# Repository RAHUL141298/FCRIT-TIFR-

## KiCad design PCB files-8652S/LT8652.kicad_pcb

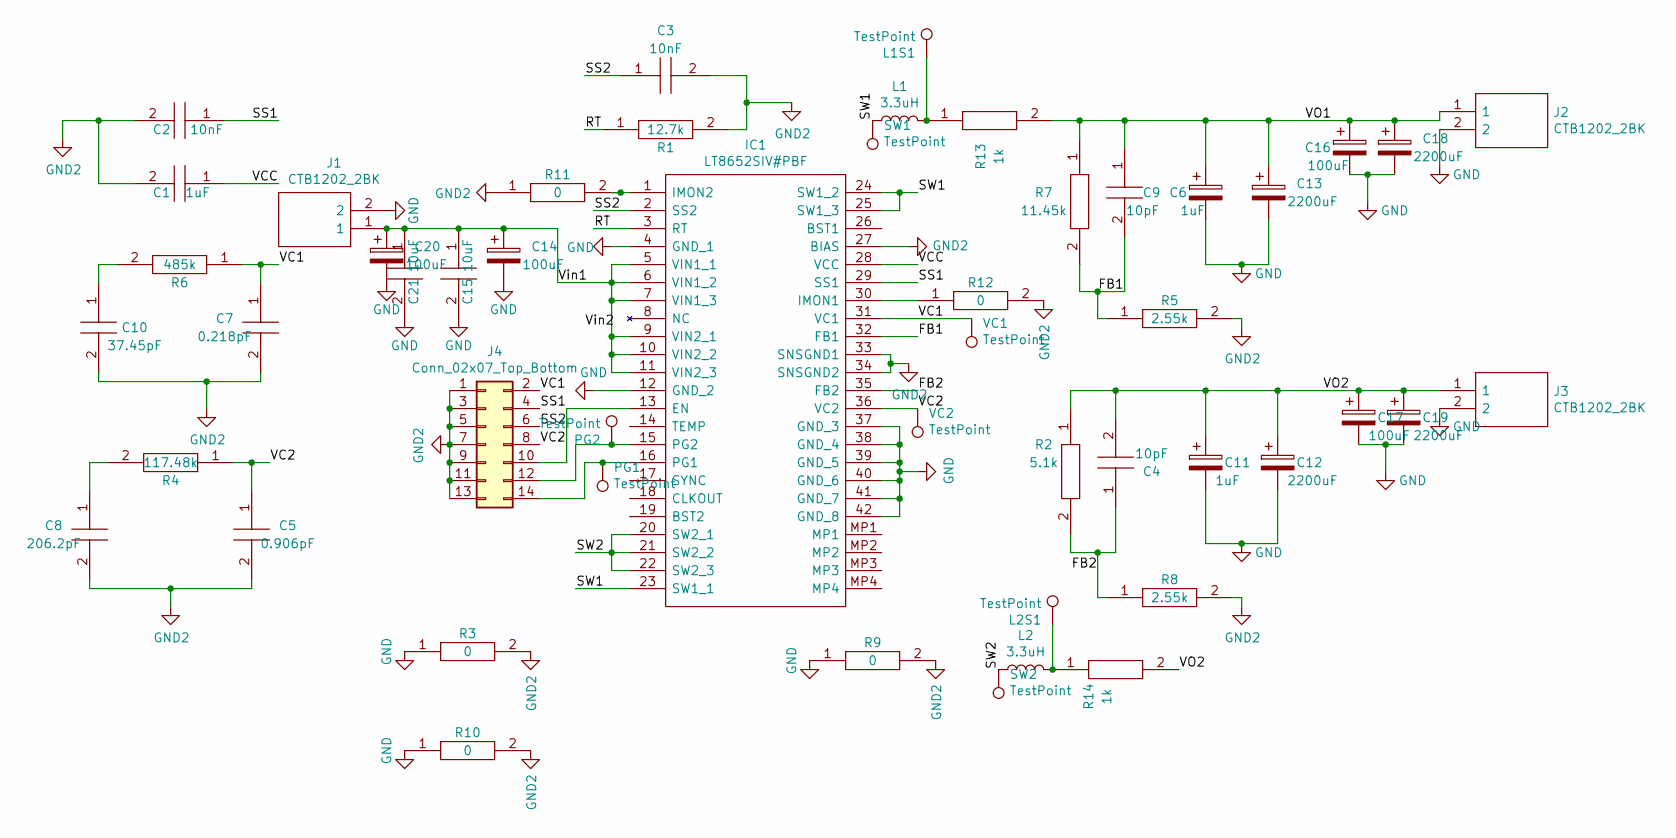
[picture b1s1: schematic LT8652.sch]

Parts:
C1: 1uF; C_0603_1608Metric_Pad1.05x0.95mm_HandSolder; Mouser Part Number 603-C0603JRNPO9BN100
C2: 10nF; C_0603_1608Metric_Pad1.05x0.95mm_HandSolder; Mouser Part Number 603-C0603JRNPO9BN100
C3: 10nF; C_0603_1608Metric_Pad1.05x0.95mm_HandSolder; Mouser Part Number 80-C0603C103K5R
C4, C9: 10pF; C_0603_1608Metric_Pad1.05x0.95mm_HandSolder; Mouser Part Number 603-C0603JRNPO9BN100
C5: 0.906pF; C_0603_1608Metric_Pad1.05x0.95mm_HandSolder; Mouser Part Number 603-C0603JRNPO9BN100
C6, C11: 1uF; C_0603_1608Metric_Pad1.05x0.95mm_HandSolder
C7: 0.218pF; C_0603_1608Metric_Pad1.05x0.95mm_HandSolder; Mouser Part Number 603-C0603JRNPO9BN100
C8: 206.2pF; C_0603_1608Metric_Pad1.05x0.95mm_HandSolder; Mouser Part Number 603-C0603JRNPO9BN100
C10: 37.45pF; C_0603_1608Metric_Pad1.05x0.95mm_HandSolder; Mouser Part Number 603-C0603JRNPO9BN100
C12, C13, C18, C19: 2200uF; CAPAE1350X1400N
C14, C20: 100uF; CP_Elec_8x10.5
C15, C21: 10uF; C_0603_1608Metric_Pad1.05x0.95mm_HandSolder; Mouser Part Number 603-C0603JRNPO9BN100
C16, C17: 100uF; C_0603_1608Metric_Pad1.05x0.95mm_HandSolder
IC1: LT8652SIV#PBF; LT8652SIVPBF; Manufacturer_Part_Number LT8652SIV#PBF
J1, J2, J3: CTB1202_2BK; TerminalBlock_TE_282834-2_1x02_P2.54mm_Horizontal; Manufacturer_Part_Number CTB1202/2BK
J4: Conn_02x07_Top_Bottom; PinHeader_2x07_P2.54mm_Vertical
L1, L2: 3.3uH; SRP1038C4R7M
L1S1, L2S1: TestPoint; TestPoint_Pad_D2.0mm
PG1, PG2: TestPoint; TestPoint_Pad_D2.0mm
R1: 12.7k; R_0603_1608Metric_Pad1.05x0.95mm_HandSolder; Manufacturer_Part_Number CRCW060312K7FKEA; Mouser Part Number 71-CRCW0603-12.7K-E3
R2: 5.1k; R_0603_1608Metric_Pad1.05x0.95mm_HandSolder; Mouser Part Number 667-ERA-2AEB512X
R3, R9, R10, R11, R12: 0; R_0603_1608Metric_Pad1.05x0.95mm_HandSolder; Mouser Part Number 756-PCF0805R2K55BI
R4: 117.48k; R_0603_1608Metric_Pad1.05x0.95mm_HandSolder; Mouser Part Number 756-PCF0805R2K55BI
R5, R8: 2.55k; R_0603_1608Metric_Pad1.05x0.95mm_HandSolder; Mouser Part Number 756-PCF0805R2K55BI
R6: 485k; R_0603_1608Metric_Pad1.05x0.95mm_HandSolder; Mouser Part Number 756-PCF0805R2K55BI
R7: 11.45k; R_0603_1608Metric_Pad1.05x0.95mm_HandSolder; Mouser Part Number 667-ERA-2AEB512X
R13, R14: 1k; R_2512_6332Metric_Pad1.52x3.35mm_HandSolder; Mouser Part Number 667-ERA-2AEB512X
SW1, SW2: TestPoint; TestPoint_Pad_D2.0mm
VC1, VC2: TestPoint; TestPoint_Pad_D2.0mm

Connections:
/FB1: C9.2, IC1.32 (FB1), R5.1, R7.2
/FB2: C4.1, IC1.35 (FB2), R2.2, R8.1
/RT: IC1.3 (RT), R1.1
/SS1: C2.1, IC1.29 (SS1), J4.4
/SS2: C3.1, IC1.2 (SS2), J4.6
/SW1: IC1.23 (SW1_1), IC1.24 (SW1_2), IC1.25 (SW1_3), L1.1, SW1.1
/SW2: IC1.20 (SW2_1), IC1.21 (SW2_2), IC1.22 (SW2_3), L2.1, SW2.1
/VC1: C7.1, IC1.31 (VC1), J4.2, R6.1, VC1.1
/VC2: C5.1, IC1.36 (VC2), J4.8, R4.1, VC2.1
/VCC: C1.1, IC1.28 (VCC)
/VO1: C6.1, C9.1, C13.1, C16.1, C18.1, J2.1, R7.1, R13.2
/VO2: C4.2, C11.1, C12.1, C17.1, C19.1, J3.1, R2.1, R14.2
/Vin1: C14.1, C15.1, C20.1, C21.1, IC1.5 (VIN1_1), IC1.6 (VIN1_2), IC1.7 (VIN1_3), IC1.9 (VIN2_1), IC1.10 (VIN2_2), IC1.11 (VIN2_3), J1.1
GND: C6.2, C11.2, C12.2, C13.2, C14.2, C15.2, C16.2, C17.2, C18.2, C19.2, C20.2, C21.2, IC1.4 (GND_1), IC1.12 (GND_2), IC1.37 (GND_3), IC1.38 (GND_4), IC1.39 (GND_5), IC1.40 (GND_6), IC1.41 (GND_7), IC1.42 (GND_8), J1.2, J2.2, J3.2, R3.1, R9.1, R10.1
GND2: C1.2, C2.2, C3.2, C5.2, C7.2, C8.2, C10.2, IC1.27 (BIAS), IC1.33 (SNSGND1), IC1.34 (SNSGND2), J4.1, J4.3, J4.5, J4.7, J4.9, J4.11, J4.13, R1.2, R3.2, R5.2, R8.2, R9.2, R10.2, R11.1, R12.2
unnamed: C8.1, R4.2
unnamed: C10.1, R6.2
unnamed: IC1.1 (IMON2), R11.2
unnamed: IC1.13 (EN), J4.10
unnamed: IC1.15 (PG2), J4.12, PG2.1
unnamed: IC1.16 (PG1), J4.14, PG1.1
unnamed: IC1.30 (IMON1), R12.1
unnamed: L1.2, L1S1.1, R13.1
unnamed: L2.2, L2S1.1, R14.1

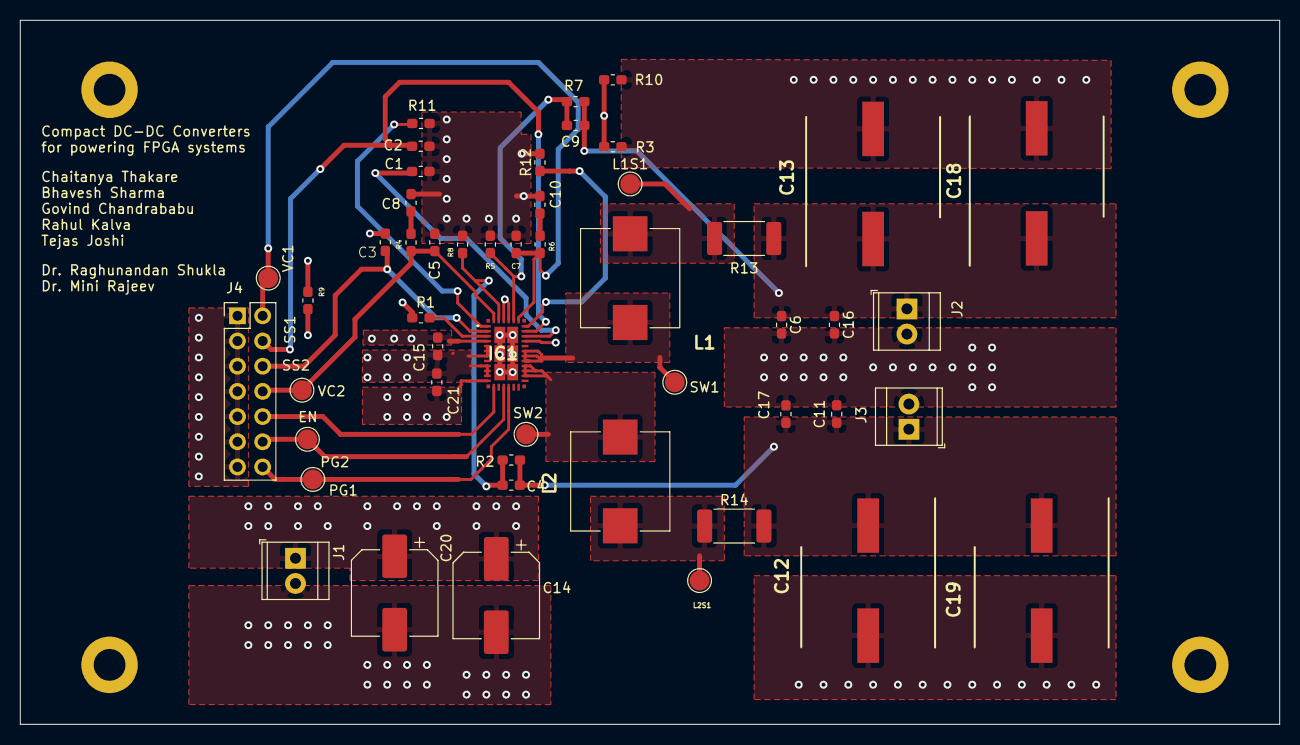
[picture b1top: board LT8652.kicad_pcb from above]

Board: 4 copper layers, 127.0 x 71.0 mm, 50 parts (0 on the bottom side), 24 nets.

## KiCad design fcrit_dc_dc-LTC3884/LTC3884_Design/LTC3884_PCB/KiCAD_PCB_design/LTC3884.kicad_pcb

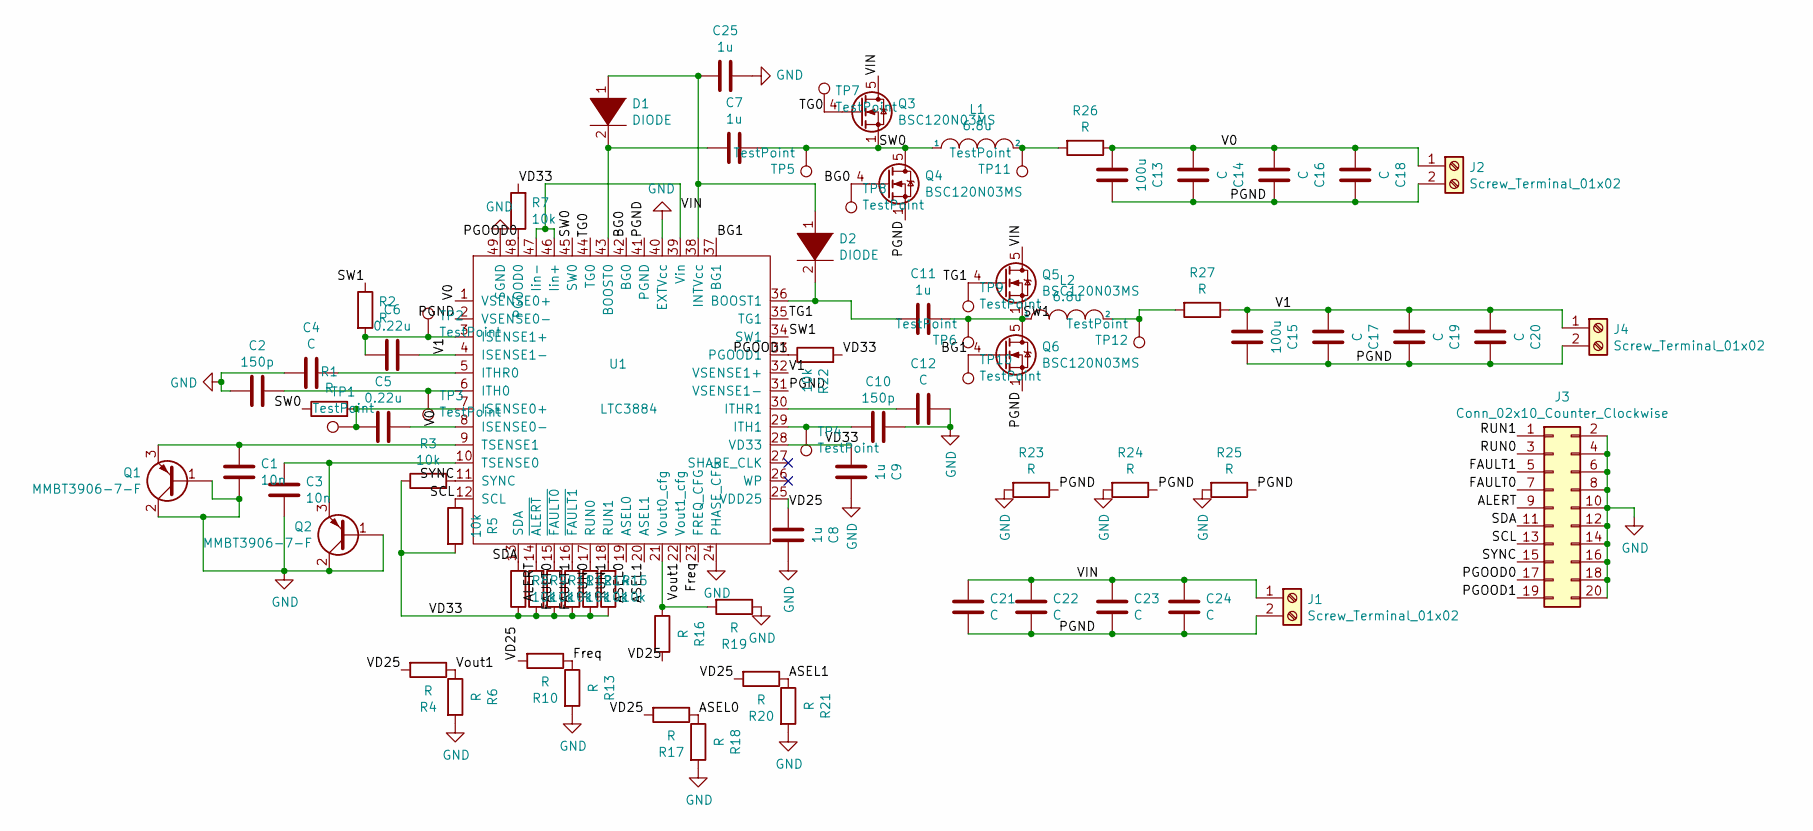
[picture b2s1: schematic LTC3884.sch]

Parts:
C1, C3: 10n; C_0603_1608Metric_Pad1.05x0.95mm_HandSolder
C2, C10: 150p; C_0603_1608Metric_Pad1.05x0.95mm_HandSolder
C4, C12, C16, C18, C19, C20, C23, C24: C; C_0603_1608Metric_Pad1.05x0.95mm_HandSolder
C5, C6: 0.22u; C_0603_1608Metric_Pad1.05x0.95mm_HandSolder
C7, C8, C9, C11, C25: 1u; C_0603_1608Metric_Pad1.05x0.95mm_HandSolder
C13, C15: 100u; CP_Elec_6.3x5.8
C14, C17, C21, C22: C; CP_Elec_6.3x5.8
D1, D2: DIODE; SOD2513X120N
J1, J2, J4: Screw_Terminal_01x02; TerminalBlock_TE_282834-2_1x02_P2.54mm_Horizontal
J3: Conn_02x10_Counter_Clockwise; PinHeader_2x10_P2.54mm_Vertical
L1, L2: 6.8u; SRP1038C6R8M
Q1, Q2: MMBT3906-7-F; SOT96P240X110-3N
Q3, Q4, Q5, Q6: BSC120N03MS; TDSON-8-1
R1, R2, R4, R6, R10, R13, R16, R17, R18, R19, R20, R21, R23, R24, R25: R; R_0603_1608Metric_Pad1.05x0.95mm_HandSolder
R3, R5, R7, R8, R9, R11, R12, R14, R15, R22: 10k; R_0603_1608Metric_Pad1.05x0.95mm_HandSolder
R26, R27: R; R_2512_6332Metric_Pad1.52x3.35mm_HandSolder
TP1, TP2, TP3, TP4, TP5, TP6, TP7, TP8, TP9, TP10, TP11, TP12: TestPoint; TestPoint_Pad_D2.0mm
U1: LTC3884; QFN-48-1EP_7x7mm_P0.5mm_EP5.15x5.15mm

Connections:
/ALERT: J3.9, R9.2, U1.14 (~ALERT)
/ASEL0: R17.1, R18.1, U1.19 (ASEL0)
/ASEL1: R20.1, R21.1, U1.20 (ASEL1)
/BG0: Q4.4 (G), TP8.1, U1.42 (BG0)
/BG1: Q6.4 (G), TP10.1, U1.37 (BG1)
/FAULT0: J3.7, R11.2, U1.15 (~FAULT0)
/FAULT1: J3.5, R12.2, U1.16 (~FAULT1)
/Freq: R10.1, R13.1, U1.23 (FREQ_CFG)
/PGND: C13.2, C14.2, C15.2, C16.2, C17.2, C18.2, C19.2, C20.2, C21.2, C22.2, C23.2, C24.2, J1.2, J2.2, J4.2, Q4.1 (S), Q4.2 (S), Q4.3 (S), Q6.1 (S), Q6.2 (S), Q6.3 (S), R23.1, R24.1, R25.1, U1.2 (VSENSE0-), U1.31 (VSENSE1-), U1.41 (PGND)
/PGOOD0: J3.17, R7.1, U1.48 (PGOOD0)
/PGOOD1: J3.19, R22.1, U1.33 (PGOOD1)
/RUN0: J3.3, R14.2, U1.17 (RUN0)
/RUN1: J3.1, R15.2, U1.18 (RUN1)
/SCL: J3.13, R5.1, U1.12 (SCL)
/SDA: J3.11, R8.2, U1.13 (SDA)
/SW0: C7.2, L1.1, Q3.1 (S), Q3.2 (S), Q3.3 (S), Q4.5 (D), R1.1, TP5.1, U1.45 (SW0)
/SW1: C11.2, L2.1, Q5.1 (S), Q5.2 (S), Q5.3 (S), Q6.5 (D), R2.1, TP6.1, U1.34 (SW1)
/SYNC: J3.15, R3.2, U1.11 (SYNC)
/TG0: Q3.4 (G), TP7.1, U1.44 (TG0)
/TG1: Q5.4 (G), TP9.1, U1.35 (TG1)
/V0: C5.2, C13.1, C14.1, C16.1, C18.1, J2.1, R26.1, U1.1 (VSENSE0+), U1.8 (ISENSE0-)
/V1: C6.2, C15.1, C17.1, C19.1, C20.1, J4.1, R27.1, U1.4 (ISENSE1-), U1.32 (VSENSE1+)
/VD25: C8.2, R4.2, R10.2, R16.2, R17.2, R20.2, U1.25 (VDD25)
/VD33: C9.2, R3.1, R5.2, R7.2, R8.1, R9.1, R11.1, R12.1, R14.1, R15.1, R22.2, U1.28 (VD33)
/VIN: C21.1, C22.1, C23.1, C24.1, J1.1, Q3.5 (D), Q5.5 (D), U1.39 (Vin), U1.46 (Iin+), U1.47 (Iin-)
/Vout1: R4.1, R6.1, U1.22 (Vout1_cfg)
GND: C1.2, C2.1, C3.2, C4.1, C8.1, C9.1, C10.2, C12.2, C25.2, J3.2, J3.4, J3.6, J3.8, J3.10, J3.12, J3.14, J3.16, J3.18, J3.20, Q1.1 (B), Q1.2 (C), Q2.1 (B), Q2.2 (C), R6.2, R13.2, R18.2, R19.1, R21.2, R23.2, R24.2, R25.2, U1.24 (PHASE_CFG), U1.40 (EXTVcc), U1.49 (SGND)
unnamed: C1.1, Q1.3 (E), U1.9 (TSENSE1)
unnamed: C2.2, TP3.1, U1.6 (ITH0)
unnamed: C3.1, Q2.3 (E), U1.10 (TSENSE0)
unnamed: C4.2, U1.5 (ITHR0)
unnamed: C5.1, R1.2, TP1.1, U1.7 (ISENSE0+)
unnamed: C6.1, R2.2, TP2.1, U1.3 (ISENSE1+)
unnamed: C7.1, D1.2 (A), U1.43 (BOOST0)
unnamed: C10.1, TP4.1, U1.29 (ITH1)
unnamed: C11.1, D2.2 (A), U1.36 (BOOST1)
unnamed: C12.1, U1.30 (ITHR1)
unnamed: C25.1, D1.1 (K), D2.1 (K), U1.38 (INTVcc)
unnamed: L1.2, R26.2, TP11.1
unnamed: L2.2, R27.2, TP12.1
unnamed: R16.1, R19.2, U1.21 (Vout0_cfg)

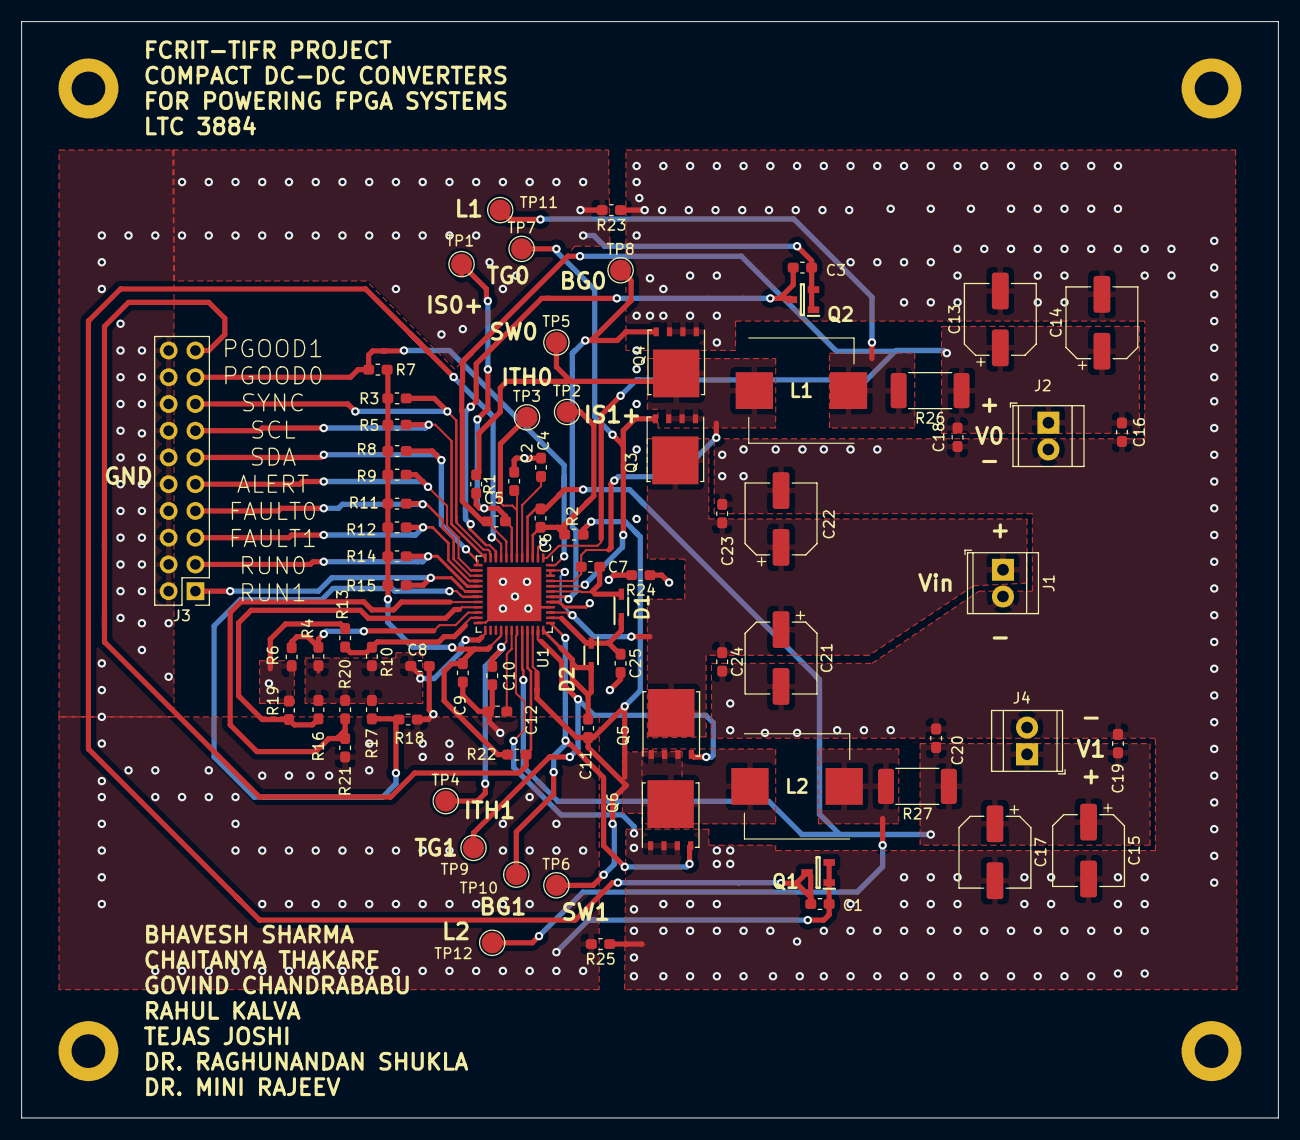
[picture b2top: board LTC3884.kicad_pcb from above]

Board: 4 copper layers, 119.4 x 104.1 mm, 79 parts (0 on the bottom side), 41 nets.

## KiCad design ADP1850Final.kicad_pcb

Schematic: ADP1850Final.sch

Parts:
C1, C16, C17: 6.8pF; C_0603_1608Metric_Pad1.05x0.95mm_HandSolder; Mouser Part Number 81-GRM33R6YA104KE14D
C2, C3, C8, C9: 1uF; C_0603_1608Metric_Pad1.05x0.95mm_HandSolder; Mouser Part Number 80-C0603C105K8R
C4, C5, C18, C19: 100uF; CP_Elec_6.3x5.8; Manufacturer_Part_Number EEHZA1V101P
C6: 68pF; C_0603_1608Metric_Pad1.05x0.95mm_HandSolder; Mouser Part Number 81-GRM33R6YA104KE14D
C7: 0.1nF; C_0603_1608Metric_Pad1.05x0.95mm_HandSolder; Mouser Part Number 81-GRM33R6YA104KE14D
C10: 1.5nF; C_0603_1608Metric_Pad1.05x0.95mm_HandSolder; Mouser Part Number 81-GRM33R6YA104KE14D
C11: 1nF; C_0603_1608Metric_Pad1.05x0.95mm_HandSolder; Mouser Part Number 81-GRM33R6YA104KE14D
C12: 56nF; C_0603_1608Metric_Pad1.05x0.95mm_HandSolder; Mouser Part Number 710-885012006022
C13: 56nF; C_0603_1608Metric_Pad1.05x0.95mm_HandSolder; Manufacturer_Part_Number 885012006023
C14, C15: 100nF; C_0603_1608Metric_Pad1.05x0.95mm_HandSolder; Mouser Part Number 80-C0603C103K5R
C20: C15; CP_Elec_6.3x5.8; Manufacturer_Part_Number EEHZA1V101P
C21: C16; CP_Elec_6.3x5.8; Manufacturer_Part_Number EEHZA1V101P
C22: C18; C_0603_1608Metric_Pad1.05x0.95mm_HandSolder; Mouser Part Number 81-GRM33R6YA104KE14D
C23: C17; C_0603_1608Metric_Pad1.05x0.95mm_HandSolder; Mouser Part Number 81-GRM33R6YA104KE14D
C24: C20; C_0603_1608Metric_Pad1.05x0.95mm_HandSolder; Mouser Part Number 81-GRM33R6YA104KE14D
C25: C19; C_0603_1608Metric_Pad1.05x0.95mm_HandSolder; Mouser Part Number 81-GRM33R6YA104KE14D
IC1: ADP1850ACPZ-R7; QFN50P500X500X75-33N; Mouser Part Number 584-ADP1850ACPZ-R7
IC2, IC3: SRP5050FA-6R8M; SRP1038C6R8M; Mouser Part Number 652-SRP5050FA-6R8M
J1, J2, J3: Screw_Terminal_01x02; TerminalBlock_TE_282834-2_1x02_P2.54mm_Horizontal
J4: Lower; SOP-8_3.9x4.9mm_P1.27mm
J5: Upper; SOP-8_3.9x4.9mm_P1.27mm
R1: 14.3k; R_0603_1608Metric_Pad1.05x0.95mm_HandSolder; Mouser Part Number 667-ERA-6ARB1432V
R2: 21.5k; R_0603_1608Metric_Pad1.05x0.95mm_HandSolder; Mouser Part Number 667-ERA-6ARB1432V
R3: 86.6k; R_0603_1608Metric_Pad1.05x0.95mm_HandSolder; Mouser Part Number 71-CRCW0805-86.6K-E3
R4, R5: 280k; R_0603_1608Metric_Pad1.05x0.95mm_HandSolder; Mouser Part Number 667-ERJ-3EKF2803V
R6, R7: 4.3k; R_0603_1608Metric_Pad1.05x0.95mm_HandSolder; Mouser Part Number 756-PCF0805PR4K3BT1
R8, R9: 0K; R_0603_1608Metric_Pad1.05x0.95mm_HandSolder; Mouser Part Number 756-PCF0805PR4K3BT1
R10, R12, R13: 2.55k; R_0603_1608Metric_Pad1.05x0.95mm_HandSolder; Mouser Part Number 756-PCF0805R2K55BI
R11: 5.1k; R_0603_1608Metric_Pad1.05x0.95mm_HandSolder; Mouser Part Number 667-ERA-2AEB512X

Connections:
/1uFA: C8.1, C9.1, IC1.2 (SYNC), IC1.4 (VCCO), IC1.5 (VDL), IC1.9 (TRK2), IC1.32 (TRK1)
/COMP1: C7.1, C10.1, IC1.30 (COMP1)
/COMP2: C6.1, C11.1, IC1.11 (COMP2)
/FB1: IC1.31 (FB1), R10.2, R13.1
/FB2: IC1.10 (FB2), R11.2, R12.1
/G1: IC1.23 (DH1); also elsewhere on the board
/G2: IC1.21 (DL1); also elsewhere on the board
/G3: IC1.18 (DH2); also elsewhere on the board
/G4: IC1.20 (DL2); also elsewhere on the board
/ILM1: C17.1, IC1.26 (ILIM1), R7.1
/ILM2: C16.1, IC1.15 (ILIM2), R6.1
/PGOOD1: IC1.27 (PGOOD1)
/PGOOD2: IC1.14 (PGOOD2)
/SW1: C15.2, IC1.24 (SW1), IC2.1, R7.2; also elsewhere on the board
/SW2: C14.2, IC1.17 (SW2), IC3.1, R6.2; also elsewhere on the board
/VO1: C18.1, C20.1, C22.1, C24.1, IC2.2, J2.1, R10.1
/VO2: C19.1, C21.1, C23.1, C25.1, IC3.2, J3.1, R11.1
/Vin: C1.1, C2.1, C3.1, C4.1, C5.1, IC1.1 (EN1), IC1.3 (VIN), IC1.8 (EN2), J1.1, R4.2, R5.2; also elsewhere on the board
GND: C6.2, C7.2, C8.2, C12.2, C13.2, IC1.6 (AGND), IC1.33 (EP), R1.2, R2.2, R3.2, R8.1, R9.1, R12.2, R13.2
unnamed: C10.2, R1.1
unnamed: C11.2, R2.1
unnamed: C12.1, IC1.13 (SS2)
unnamed: C13.1, IC1.28 (SS1)
unnamed: C14.1, IC1.16 (BST2)
unnamed: C15.1, IC1.25 (BST1)
unnamed: IC1.7 (FREQ), R3.1
unnamed: IC1.12 (RAMP2), R4.1
unnamed: IC1.29 (RAMP1), R5.1
PGND: C1.2, C2.2, C3.2, C4.2, C5.2, C9.2, C16.2, C17.2, C18.2, C19.2, C20.2, C21.2, C22.2, C23.2, C24.2, C25.2, IC1.19 (PGND2), IC1.22 (PGND1), J1.2, J2.2, J3.2, R8.2, R9.2; also elsewhere on the board

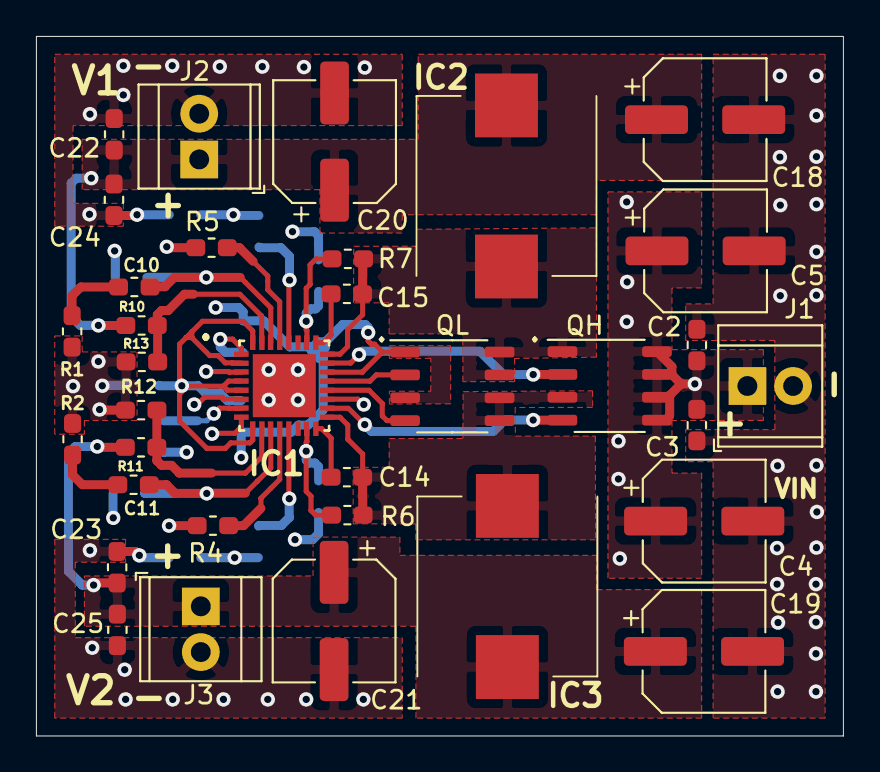
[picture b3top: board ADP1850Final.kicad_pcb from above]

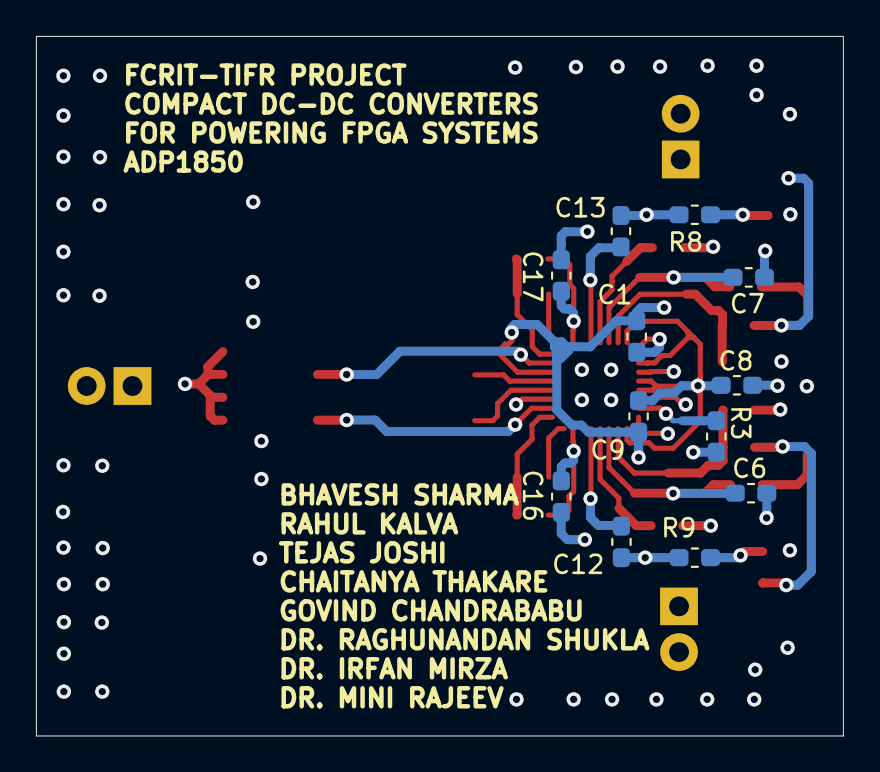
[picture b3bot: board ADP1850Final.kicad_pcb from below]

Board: 4 copper layers, 44.8 x 38.9 mm, 46 parts (12 on the bottom side), 27 nets.

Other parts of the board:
QH: Upper; SOP-8_3.9x4.9mm_P1.27mm
QL: Lower; SOP-8_3.9x4.9mm_P1.27mm

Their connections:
/G1: QH.2; also elsewhere on the board
/G2: QL.2; also elsewhere on the board
/G3: QH.4; also elsewhere on the board
/G4: QL.4; also elsewhere on the board
/SW1: QH.1, QL.7, QL.8; also elsewhere on the board
/SW2: QH.3, QL.5, QL.6; also elsewhere on the board
/Vin: QH.5, QH.6, QH.7, QH.8; also elsewhere on the board
PGND: QL.1, QL.3; also elsewhere on the board
